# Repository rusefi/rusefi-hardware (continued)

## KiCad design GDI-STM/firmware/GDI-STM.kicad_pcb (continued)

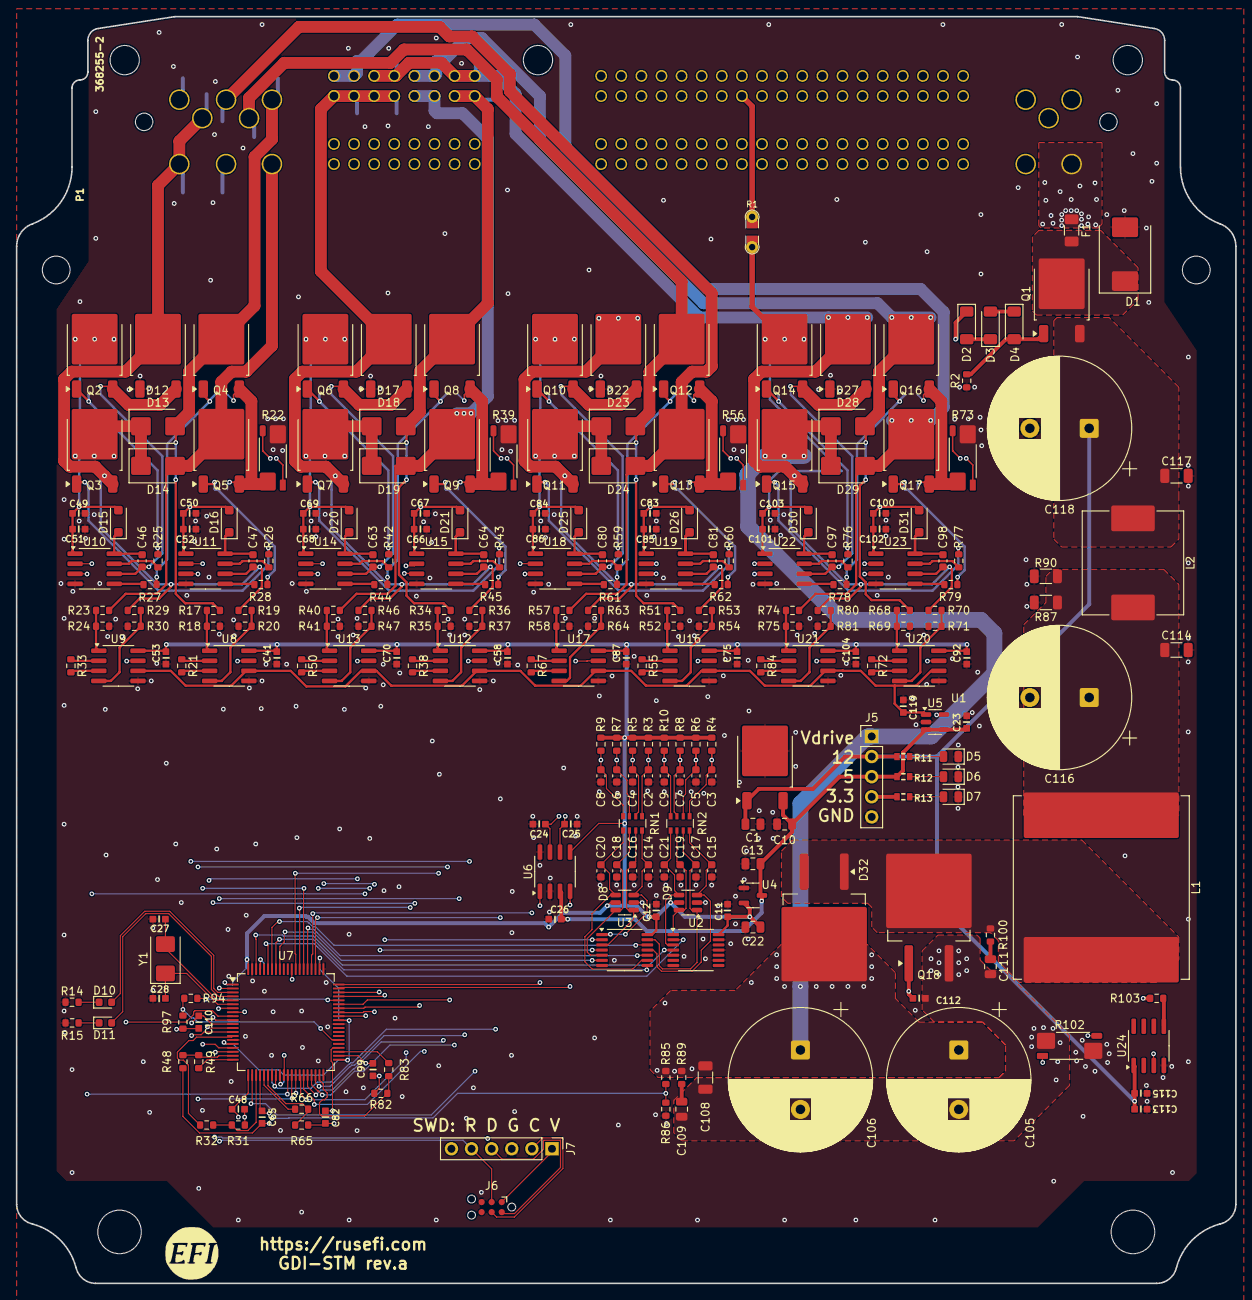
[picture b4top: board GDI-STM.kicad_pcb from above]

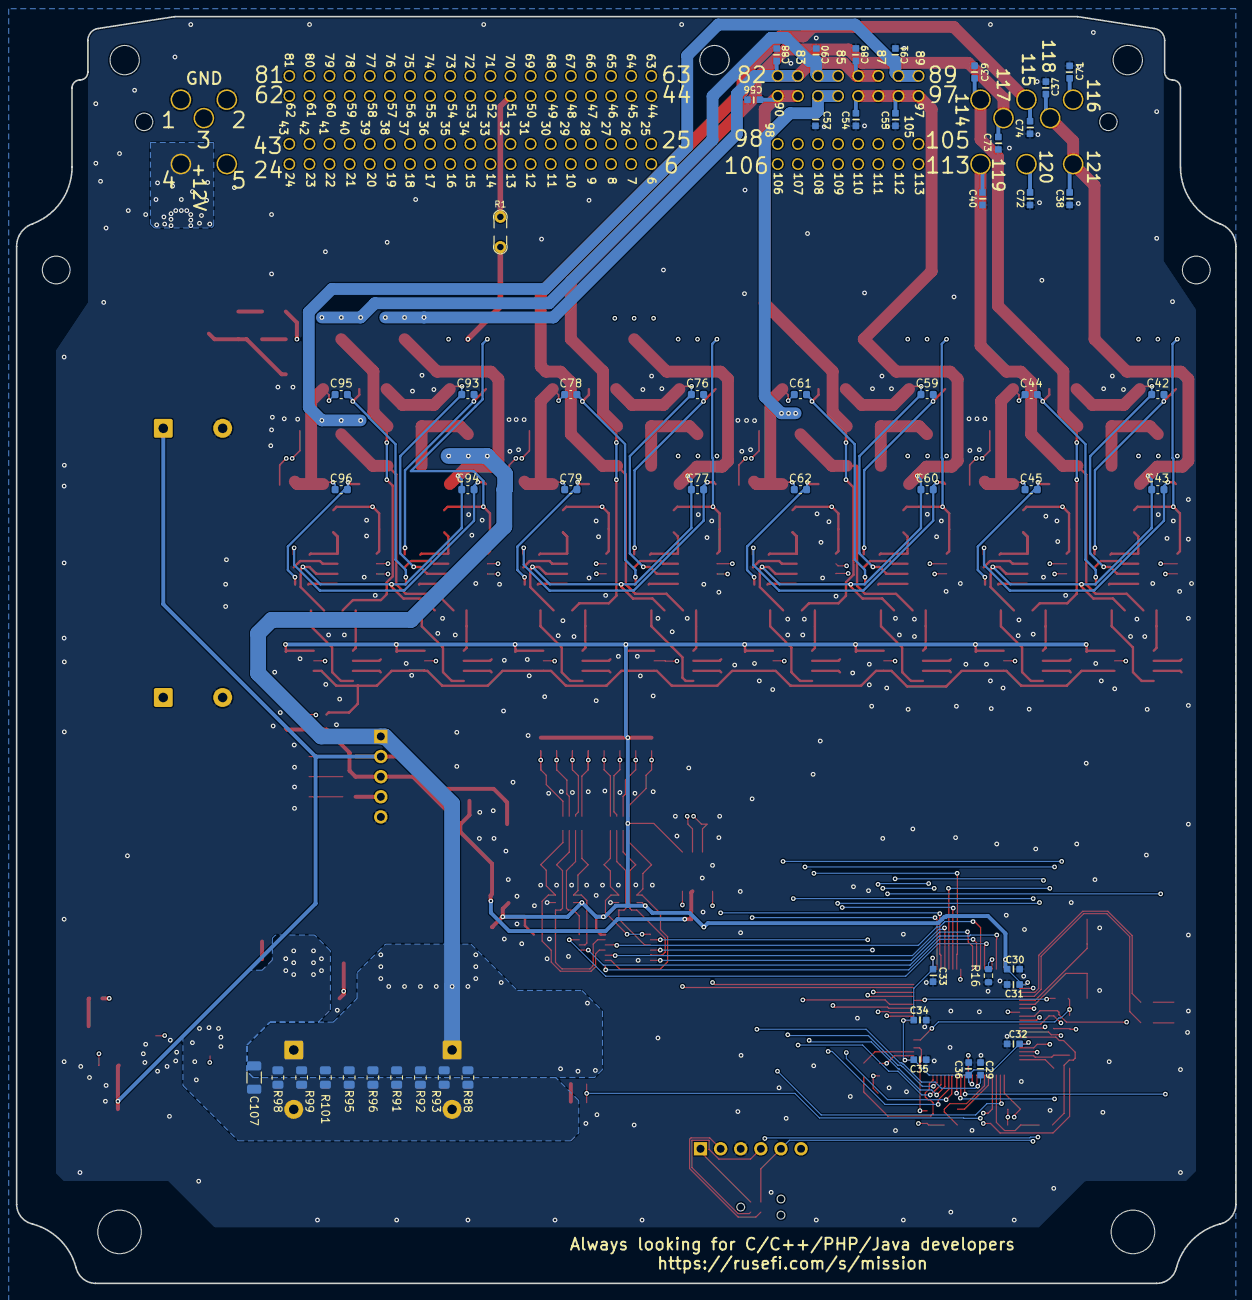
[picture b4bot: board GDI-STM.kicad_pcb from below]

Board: 4 copper layers, 154.0 x 160.0 mm, 311 parts (51 on the bottom side), 199 nets.

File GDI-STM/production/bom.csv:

Designator,Footprint,Quantity,Value,LCSC Part #
"C1, C10, C13, C22",0805,4,10u,C15850
"C100, C101, C113, C49, C50, C66, C67, C83, C84",C0603,9,1u,C15849
"C102, C103, C104, C11, C115, C119, C12, C23, C26, C29, C31, C32, C33, C34, C35, C36, C41, C51, C52, C53, C58, C68, C69, C70, C75, C85, C86, C87, C92",C0603,29,100n,C14663
"C105, C106",CP_Radial_D18.0mm_P7.50mm,2,470uF/200V,C160144
"C107, C108, C114, C117",1206,4,0.22uF,C106048
"C109, C111",0805,2,330p,C113837
"C110, C48, C65, C82, C99",C0603,5,330p,C576850
C112,C0603,1,470p,C326973
"C116, C118",CP_Radial_D18.0mm_P7.50mm,2,2200uF/50V,C106661
"C14, C15, C16, C17, C18, C19, C2, C20, C21, C3, C4, C42, C43, C44, C45, C5, C59, C6, C60, C61, C62, C7, C76, C77, C78, C79, C8, C9, C93, C94, C95, C96",0603,32,1000pF,C106247
"C24, C25",C0603,2,47p,C1671
"C27, C28",C0603,2,12p,C38523
C30,C0603,1,4.7u,C19666
"C37, C38, C39, C40, C54, C55, C56, C57, C71, C72, C73, C74, C88, C89, C90, C91",C0603,16,4700p,C327158
"C46, C47, C63, C64, C80, C81, C97, C98",0603,8,0.33uF,C1615
D1,D_SMC,1,SMCJ22CA,C151904
D10,0603,1,GREEN,C12624
D11,0603,1,RED,C2286
"D12, D17, D22, D27",TO-252-2,4,SBR10200CTL,C459529
"D13, D14, D18, D19, D23, D24, D28, D29",D_SMB,8,SS520B,C382826
"D15, D16, D20, D21, D25, D26, D30, D31",D_SOD-123F,8,ES1JFL,C719809
"D2, D3, D4",D_MiniMELF,3,ZMM5V6,C7497481
D32,TO-263-2,1,STTH802G-TR,C181034
"D5, D6, D7",0805,3,LED_Small,C2296
"D8, D9",SOT-23-6,2,SRV05-4,C85364
F1,1206,1,20A,C136357
L1,L_Changjiang_FXL2213,1,10uH,C22378757
L2,L_Changjiang_FXL1360,1,6.8uH,C7471128
P1,TE_368255-2,1,368255-2,
Q1,TO-252-2,1,AOD4185,C400894
"Q10, Q11, Q12, Q13, Q14, Q15, Q16, Q17, Q2, Q3, Q4, Q5, Q6, Q7, Q8, Q9",TO-252-2,16,IPD320N20N3G,C501515
Q18,TO-263-2,1,IPB107N20N3G,C444895
"R10, R14, R15, R18, R20, R24, R3, R30, R35, R37, R4, R41, R47, R5, R52, R54, R58, R6, R64, R69, R7, R71, R75, R8, R81, R86, R9",0603,27,1K,C21190
"R100, R89",0603,2,5.1,C25197
"R101, R88, R91, R92, R93, R95, R96, R98, R99",0805,9,360k,C17645
"R102, R22, R39, R56, R73",R_Shunt_Vishay_WSK2512_6332Metric_T1.19mm,5,0.016,C915978
"R103, R25, R26, R27, R28, R42, R43, R44, R45, R59, R60, R61, R62, R76, R77, R78, R79",0603,17,10,C22859
R11,R0603,1,5.1k,C23186
R12,R0603,1,1.6k,C22847
R13,R0603,1,750,C23241
"R16, R2",0603,2,10K,C25804
"R17, R19, R23, R29, R34, R36, R40, R46, R51, R53, R57, R63, R68, R70, R74, R80, R85",0603,17,147k,C22878
"R31, R48, R65, R82, R97",0603,5,1.02k,C22831
"R32, R49, R66, R83, R94",0603,5,7.15k,C25980
"R87, R90",1206,2,2K,C17944
"RN1, RN2",R_Array_Convex_4x0603,2,10k,C29718
U1,TO-252-2,1,LM78M05_TO252,C58069
"U10, U11, U14, U15, U18, U19, U22, U23, U24",SOIC-8_3.9x4.9mm_P1.27mm,9,IRS21867S,C52290
"U12, U13, U16, U17, U20, U21, U8, U9",SOIC-8_3.9x4.9mm_P1.27mm,8,INA826,C38433
"U2, U3",TSSOP-14_4.4x5mm_P0.65mm,2,74HC14,C5606
U4,SOT-23-3,1,XC6206P332MR,C5446
U5,SOT-23-5,1,REF2033,C440747
U6,SOIC-8_3.9x4.9mm_P1.27mm,1,TJA1051T-3,C38695
U7,LQFP-80_12x12mm_P0.5mm,1,STM32G474M_B-C-E_Tx,C5270364
Y1,Crystal_SMD_5032-2Pin_5.0x3.2mm,1,20MHz,C112566

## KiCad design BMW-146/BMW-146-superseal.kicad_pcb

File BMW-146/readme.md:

# N54

E9x 2006 to 2010 with "35" engine would be N54

For some years they had both N54 and N55 depending on trim. 335is would be N54, N55 would be newer engine with 204 pin ECU

https://rusefi.com/docs/pinouts/BMW-E92/

https://github.com/rusefi/rusefi_documentation/blob/master/OEM-Docs/Bmw/2010%20BMW%20335i%20Coupe%20(E92)%20N54.pdf

# offtopic

https://github.com/rusefi/rusefi_documentation/blob/master/OEM-Docs/Bmw/2009%20BMW%20328i%20Sedan%20(E90)%203.0%20N51.pdf

https://github.com/rusefi/rusefi_documentation/blob/master/OEM-Docs/Bmw/2009%20BMW%20335i%20Sedan%20(E90)%203.0%20N53.pdf

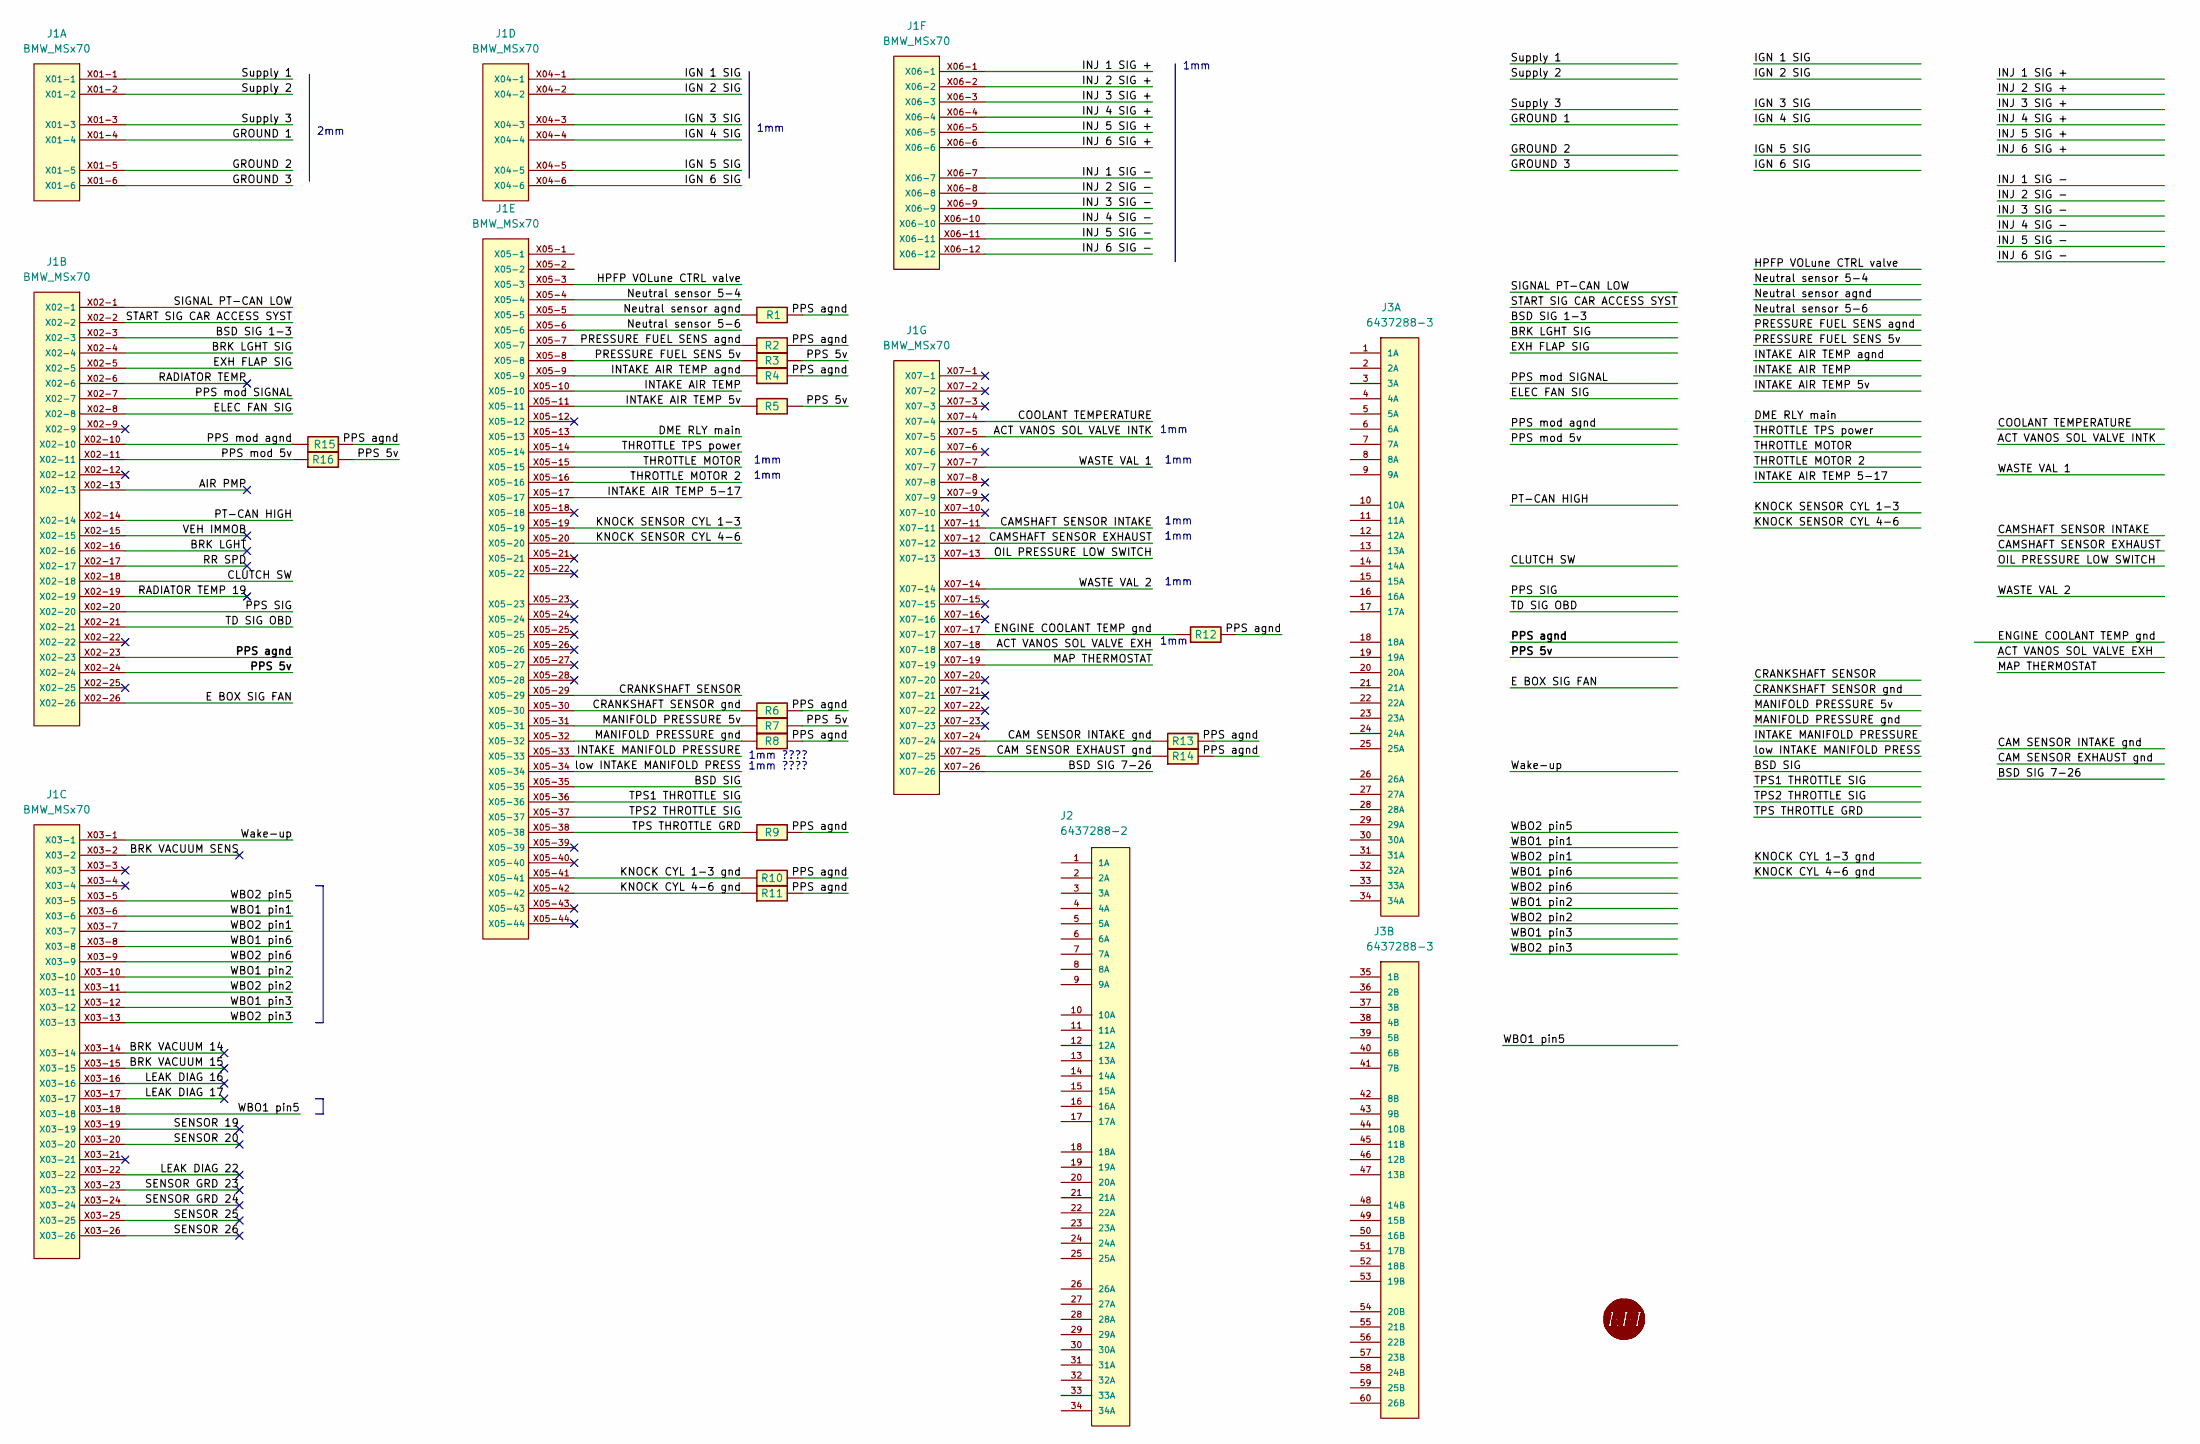
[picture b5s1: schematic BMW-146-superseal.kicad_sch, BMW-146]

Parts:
G1, G2: RUSEFI_LOGO; rusefi_logo
J1: BMW_MSx70
J2: 6437288-2; LCSC C591852
J3: 6437288-3; TE_6437288-3
R1, R2, R3, R4, R5, R6, R7, R8, R9, R10, R11, R12, R13, R14, R15, R16: 0R; R0603

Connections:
/ACT VANOS SOL VALVE EXH: J1.X07-18
/ACT VANOS SOL VALVE INTK: J1.X07-5
/AIR PMP: J1.X02-13
/BRK LGHT: J1.X02-16
/BRK LGHT SIG: J1.X02-4
/BRK VACUUM 14: J1.X03-14
/BRK VACUUM 15: J1.X03-15
/BRK VACUUM SENS: J1.X03-2
/BSD SIG: J1.X05-35
/BSD SIG 1-3: J1.X02-3
/BSD SIG 7-26: J1.X07-26
/CAM SENSOR EXHAUST gnd: J1.X07-25, R14.1
/CAM SENSOR INTAKE gnd: J1.X07-24, R13.1
/CAMSHAFT SENSOR EXHAUST: J1.X07-12
/CAMSHAFT SENSOR INTAKE: J1.X07-11
/CLUTCH SW: J1.X02-18
/COOLANT TEMPERATURE: J1.X07-4
/CRANKSHAFT SENSOR: J1.X05-29
/CRANKSHAFT SENSOR gnd: J1.X05-30, R6.1
/DME RLY main: J1.X05-13
/E BOX SIG FAN: J1.X02-26
/ELEC FAN SIG: J1.X02-8
/ENGINE COOLANT TEMP gnd: J1.X07-17, R12.1
/EXH FLAP SIG: J1.X02-5
/GROUND 1: J1.X01-4
/GROUND 2: J1.X01-5
/GROUND 3: J1.X01-6
/HPFP VOLune CTRL valve: J1.X05-3
/IGN 1 SIG: J1.X04-1
/IGN 2 SIG: J1.X04-2
/IGN 3 SIG: J1.X04-3
/IGN 4 SIG: J1.X04-4
/IGN 5 SIG: J1.X04-5
/IGN 6 SIG: J1.X04-6
/INJ 1 SIG +: J1.X06-1
/INJ 1 SIG -: J1.X06-7
/INJ 2 SIG +: J1.X06-2
/INJ 2 SIG -: J1.X06-8
/INJ 3 SIG +: J1.X06-3
/INJ 3 SIG -: J1.X06-9
/INJ 4 SIG +: J1.X06-4
/INJ 4 SIG -: J1.X06-10
/INJ 5 SIG +: J1.X06-5
/INJ 5 SIG -: J1.X06-11
/INJ 6 SIG +: J1.X06-6
/INJ 6 SIG -: J1.X06-12
/INTAKE AIR TEMP: J1.X05-10
/INTAKE AIR TEMP 5-17: J1.X05-17
/INTAKE AIR TEMP 5v: J1.X05-11, R5.1
/INTAKE AIR TEMP agnd: J1.X05-9, R4.1
/INTAKE MANIFOLD PRESSURE: J1.X05-33
/KNOCK CYL 1-3 gnd: J1.X05-41, R10.1
/KNOCK CYL 4-6 gnd: J1.X05-42, R11.1
/KNOCK SENSOR CYL 1-3: J1.X05-19
/KNOCK SENSOR CYL 4-6: J1.X05-20
/LEAK DIAG 16: J1.X03-16
/LEAK DIAG 17: J1.X03-17
/LEAK DIAG 22: J1.X03-22
/MANIFOLD PRESSURE 5v: J1.X05-31, R7.1
/MANIFOLD PRESSURE gnd: J1.X05-32, R8.1
/MAP THERMOSTAT: J1.X07-19
/Neutral sensor 5-4: J1.X05-4
/Neutral sensor 5-6: J1.X05-6
/Neutral sensor agnd: J1.X05-5, R1.1
/OIL PRESSURE LOW SWITCH: J1.X07-13
/PPS 5v: J1.X02-24, R3.2, R5.2, R7.2, R16.2
/PPS SIG: J1.X02-20
/PPS agnd: J1.X02-23, R1.2, R2.2, R4.2, R6.2, R8.2, R9.2, R10.2, R11.2, R12.2, R13.2, R14.2, R15.2
/PPS mod 5v: J1.X02-11, R16.1
/PPS mod SIGNAL: J1.X02-7
/PPS mod agnd: J1.X02-10, R15.1
/PRESSURE FUEL SENS 5v: J1.X05-8, R3.1
/PRESSURE FUEL SENS agnd: J1.X05-7, R2.1
/PT-CAN HIGH: J1.X02-14
/RADIATOR TEMP: J1.X02-6
/RADIATOR TEMP 19: J1.X02-19
/RR SPD: J1.X02-17
/SENSOR 19: J1.X03-19
/SENSOR 20: J1.X03-20
/SENSOR 25: J1.X03-25
/SENSOR 26: J1.X03-26
/SENSOR GRD 23: J1.X03-23
/SENSOR GRD 24: J1.X03-24
/SIGNAL PT-CAN LOW: J1.X02-1
/START SIG CAR ACCESS SYST: J1.X02-2
/Supply 1: J1.X01-1
/Supply 2: J1.X01-2
/Supply 3: J1.X01-3
/TD SIG OBD: J1.X02-21
/THROTTLE MOTOR: J1.X05-15
/THROTTLE MOTOR 2: J1.X05-16
/THROTTLE TPS power: J1.X05-14
/TPS1 THROTTLE SIG: J1.X05-36
/TPS2 THROTTLE SIG: J1.X05-37
/TPS THROTTLE GRD: J1.X05-38, R9.1
/VEH IMMOB: J1.X02-15
/WASTE VAL 1: J1.X07-7
/WASTE VAL 2: J1.X07-14
/WBO1 pin1: J1.X03-6
/WBO1 pin2: J1.X03-10
/WBO1 pin3: J1.X03-12
/WBO1 pin5: J1.X03-18
/WBO1 pin6: J1.X03-8
/WBO2 pin1: J1.X03-7
/WBO2 pin2: J1.X03-11
/WBO2 pin3: J1.X03-13
/WBO2 pin5: J1.X03-5
/WBO2 pin6: J1.X03-9
/Wake-up: J1.X03-1
/low INTAKE MANIFOLD PRESS: J1.X05-34

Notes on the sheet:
1mm
1mm ????
2mm

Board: 2 copper layers, 21 parts (1 on the bottom side), 18 nets, no tracks yet.

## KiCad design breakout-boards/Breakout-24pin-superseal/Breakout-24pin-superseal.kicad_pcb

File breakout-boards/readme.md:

# Vehicle to superseal adapter

Claim yours at https://shop.rusefi.com

* Ferrari-Maserati f136 engine 121 pins 

* Ford Mustang 198 pins

* [Hyundai 1.6 GDI PB 154 pins GDI](https://github.com/rusefi/rusefi-hardware/blob/main/breakout-boards/Breakout_154_kia_pb/hellen-hyundai-pb-154-adapter-b-schematic.pdf) [pinout](https://rusefi.com/docs/pinouts/hellen/hellen-hyundai-pb-mt/)

* Bosch me17 112 pins

* [Mazda Miata NC](https://github.com/rusefi/rusefi-hardware/blob/main/breakout-boards/Breakout-mazda-nc-0.1.pdf) [pinout](https://rusefi.com/docs/pinouts/miata-nc/)

* Mitsubishi Lancer Evo-x

* Mitsubishi Mirage

* Volkswagen Passat 2.0 MED9.1 154 pins GDI

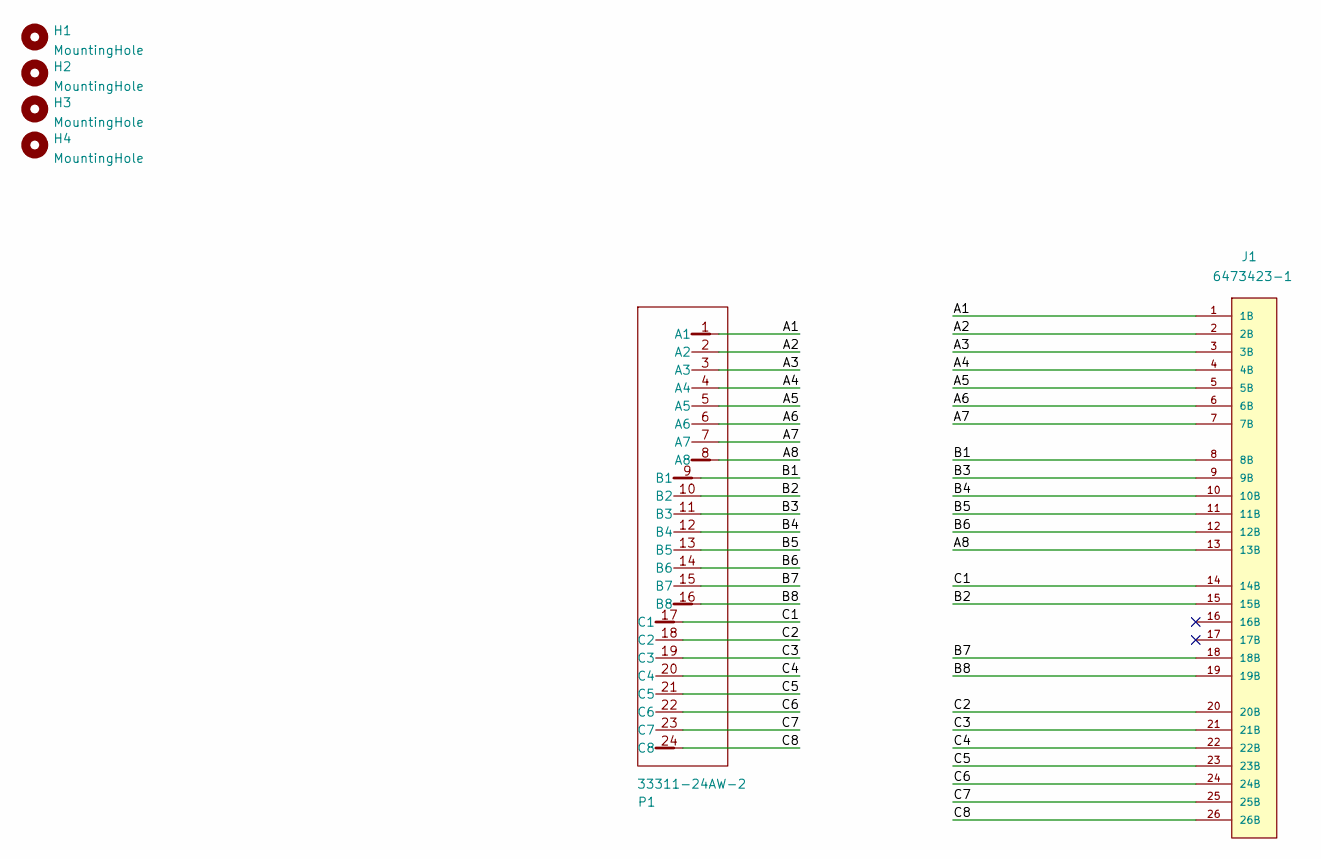
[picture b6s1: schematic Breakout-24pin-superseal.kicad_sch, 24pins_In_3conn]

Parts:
H1, H2, H3, H4: MountingHole; MountingHole_3.2mm_M3_DIN965_Pad
J1: 6473423-1
P1: 33311-24AW-2

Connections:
/A1: J1.1 (1B), P1.1 (A1)
/A2: J1.2 (2B), P1.2 (A2)
/A3: J1.3 (3B), P1.3 (A3)
/A4: J1.4 (4B), P1.4 (A4)
/A5: J1.5 (5B), P1.5 (A5)
/A6: J1.6 (6B), P1.6 (A6)
/A7: J1.7 (7B), P1.7 (A7)
/A8: J1.13 (13B), P1.8 (A8)
/B1: J1.8 (8B), P1.9 (B1)
/B2: J1.15 (15B), P1.10 (B2)
/B3: J1.9 (9B), P1.11 (B3)
/B4: J1.10 (10B), P1.12 (B4)
/B5: J1.11 (11B), P1.13 (B5)
/B6: J1.12 (12B), P1.14 (B6)
/B7: J1.18 (18B), P1.15 (B7)
/B8: J1.19 (19B), P1.16 (B8)
/C1: J1.14 (14B), P1.17 (C1)
/C2: J1.20 (20B), P1.18 (C2)
/C3: J1.21 (21B), P1.19 (C3)
/C4: J1.22 (22B), P1.20 (C4)
/C5: J1.23 (23B), P1.21 (C5)
/C6: J1.24 (24B), P1.22 (C6)
/C7: J1.25 (25B), P1.23 (C7)
/C8: J1.26 (26B), P1.24 (C8)

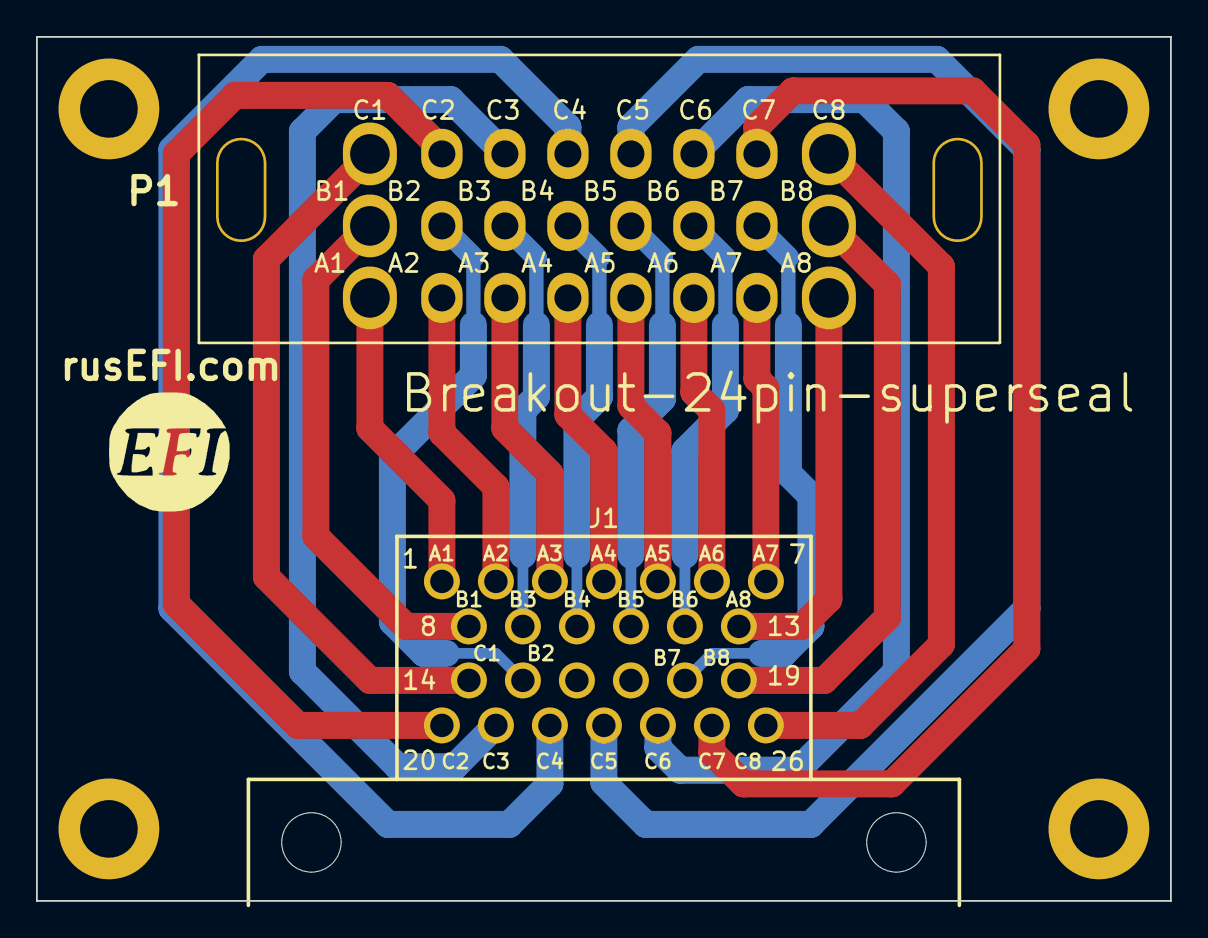
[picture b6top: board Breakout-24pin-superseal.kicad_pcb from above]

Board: 2 copper layers, 63.0 x 48.0 mm, 8 parts (1 on the bottom side), 24 nets.

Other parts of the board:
G?: LOGO
G?#2: LOGO

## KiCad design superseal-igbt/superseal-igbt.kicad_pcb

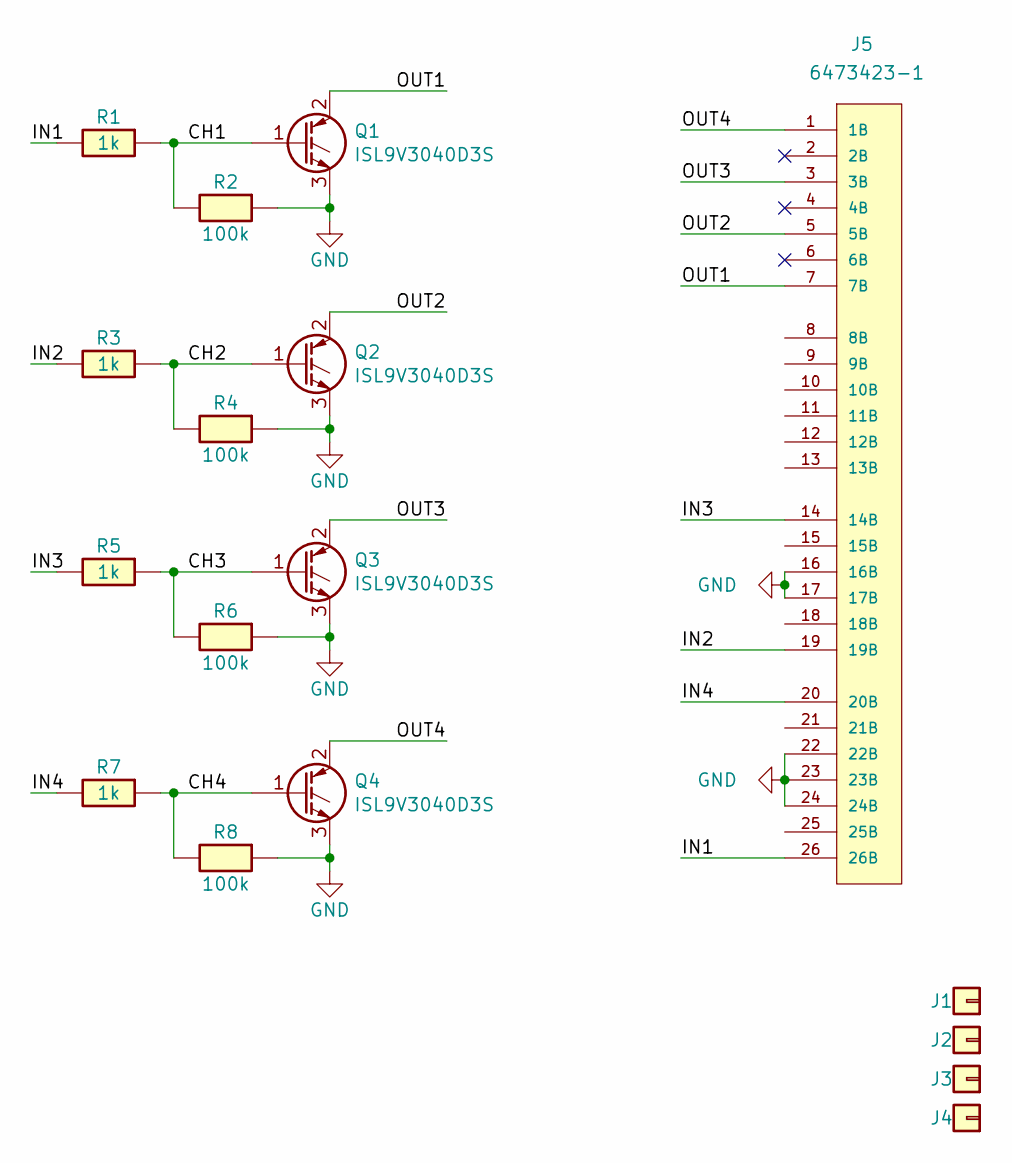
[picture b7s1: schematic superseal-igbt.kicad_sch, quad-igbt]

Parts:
J1, J2, J3, J4: Conn_01x01; MountingHole_5mm
J5: 6473423-1
Q1, Q2, Q3, Q4: ISL9V3040D3S; TO-263-2; LCSC C462128
R1, R3, R5, R7: 1k; R0805; LCSC C17513
R2, R4, R6, R8: 100k; R0805; LCSC C149504

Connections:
/CH1: Q1.1 (G), R1.1, R2.2
/CH2: Q2.1 (G), R3.1, R4.2
/CH3: Q3.1 (G), R5.1, R6.2
/CH4: Q4.1 (G), R7.1, R8.2
/IN1: J5.26 (26B), R1.2
/IN2: J5.19 (19B), R3.2
/IN3: J5.14 (14B), R5.2
/IN4: J5.20 (20B), R7.2
/OUT1: J5.7 (7B), Q1.2 (C)
/OUT2: J5.5 (5B), Q2.2 (C)
/OUT3: J5.3 (3B), Q3.2 (C)
/OUT4: J5.1 (1B), Q4.2 (C)
GND: J5.16 (16B), J5.17 (17B), J5.22 (22B), J5.23 (23B), J5.24 (24B), Q1.3 (E), Q2.3 (E), Q3.3 (E), Q4.3 (E), R2.1, R4.1, R6.1, R8.1

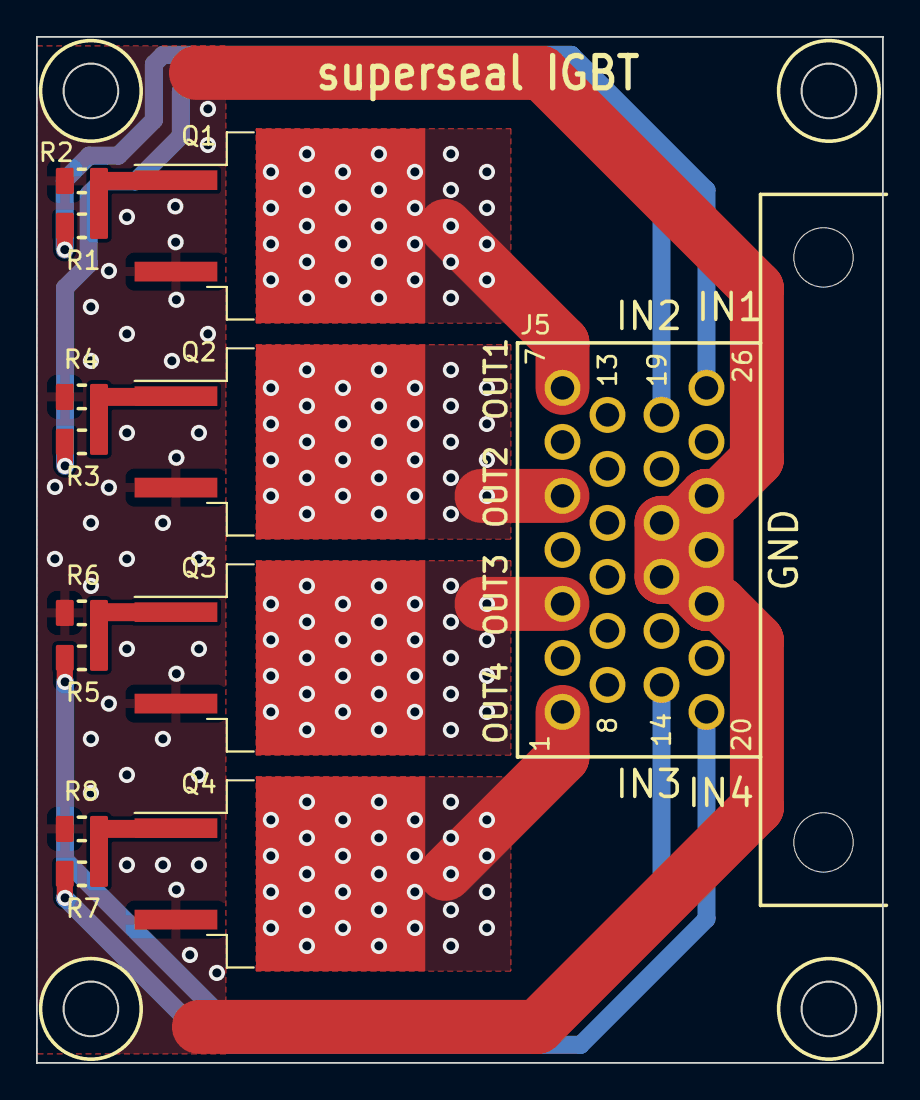
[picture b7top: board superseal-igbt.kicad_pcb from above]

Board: 2 copper layers, 47.0 x 57.0 mm, 17 parts (0 on the bottom side), 13 nets.

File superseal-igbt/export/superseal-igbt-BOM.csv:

Comment,Designator,Footprint,LCSC Part #
"6473423-1","J5","Connectors:6473423-1",""
"ISL9V3040D3S","Q1","Package_TO_SOT_SMD:TO-263-2","C462128"
"ISL9V3040D3S","Q2","Package_TO_SOT_SMD:TO-263-2","C462128"
"ISL9V3040D3S","Q3","Package_TO_SOT_SMD:TO-263-2","C462128"
"ISL9V3040D3S","Q4","Package_TO_SOT_SMD:TO-263-2","C462128"
"1k","R1","hellen-one-common:R0805","C17513"
"100k","R2","hellen-one-common:R0805","C149504"
"1k","R3","hellen-one-common:R0805","C17513"
"100k","R4","hellen-one-common:R0805","C149504"
"1k","R5","hellen-one-common:R0805","C17513"
"100k","R6","hellen-one-common:R0805","C149504"
"1k","R7","hellen-one-common:R0805","C17513"
"100k","R8","hellen-one-common:R0805","C149504"

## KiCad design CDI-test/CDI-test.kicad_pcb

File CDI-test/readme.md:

https://www.youtube.com/watch?v=ZHLb0ZEvTBY

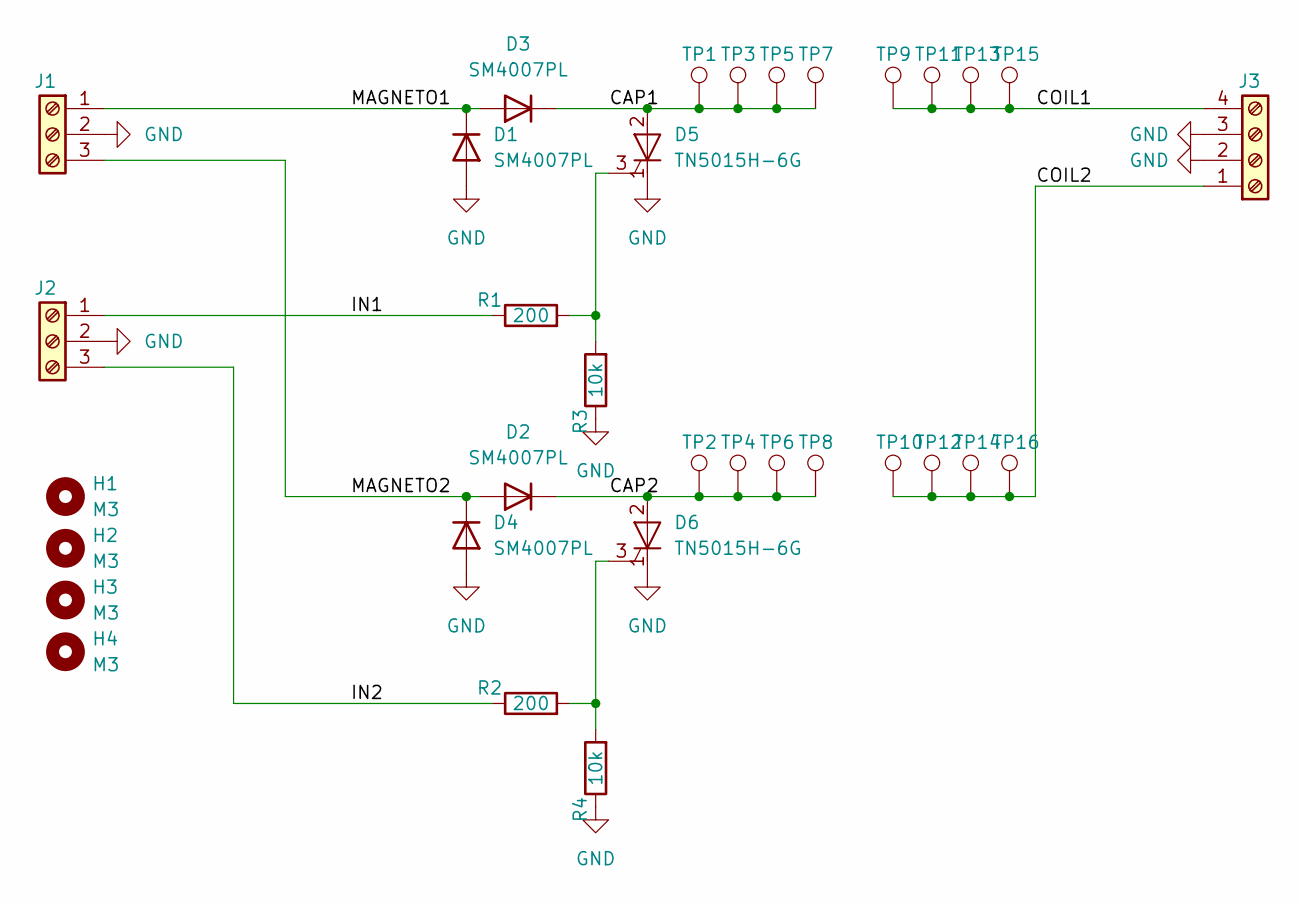
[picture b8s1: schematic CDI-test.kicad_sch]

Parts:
D1, D2, D3, D4: SM4007PL; D_SOD-123F; LCSC C64898
D5, D6: TN5015H-6G; TO-263-2; LCSC C2971185
H1, H2, H3, H4: M3; MountingHole_3.2mm_M3_Pad_Via
J1, J2: Screw_Terminal_01x03; TerminalBlock_MetzConnect_Type055_RT01503HDWU_1x03_P5.00mm_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; LCSC C557647
J3: Screw_Terminal_01x04; TerminalBlock_MetzConnect_Type055_RT01504HDWU_1x04_P5.00mm_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; LCSC C173286
R1, R2: 200; R_1206_3216Metric_Pad1.30x1.75mm_HandSolder; LCSC C2962216
R3, R4: 10k; R_1206_3216Metric_Pad1.30x1.75mm_HandSolder; LCSC C175515
TP1, TP2, TP3, TP4, TP5, TP6, TP7, TP8, TP9, TP10, TP11, TP12, TP13, TP14, TP15, TP16: SolderWire-1sqmm_1x01_D1.4mm_OD2.7mm

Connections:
/CAP1: D3.1 (K), D5.2 (A), TP1.1, TP3.1, TP5.1, TP7.1
/CAP2: D2.1 (K), D6.2 (A), TP2.1, TP4.1, TP6.1, TP8.1
/COIL1: J3.4, TP9.1, TP11.1, TP13.1, TP15.1
/COIL2: J3.1, TP10.1, TP12.1, TP14.1, TP16.1
/IN1: J2.1, R1.1
/IN2: J2.3, R2.1
/MAGNETO1: D1.1 (K), D3.2 (A), J1.1
/MAGNETO2: D2.2 (A), D4.1 (K), J1.3
GND: D1.2 (A), D4.2 (A), D5.1 (K), D6.1 (K), J1.2, J2.2, J3.2, J3.3, R3.1, R4.1
unnamed: D5.3 (G), R1.2, R3.2
unnamed: D6.3 (G), R2.2, R4.2

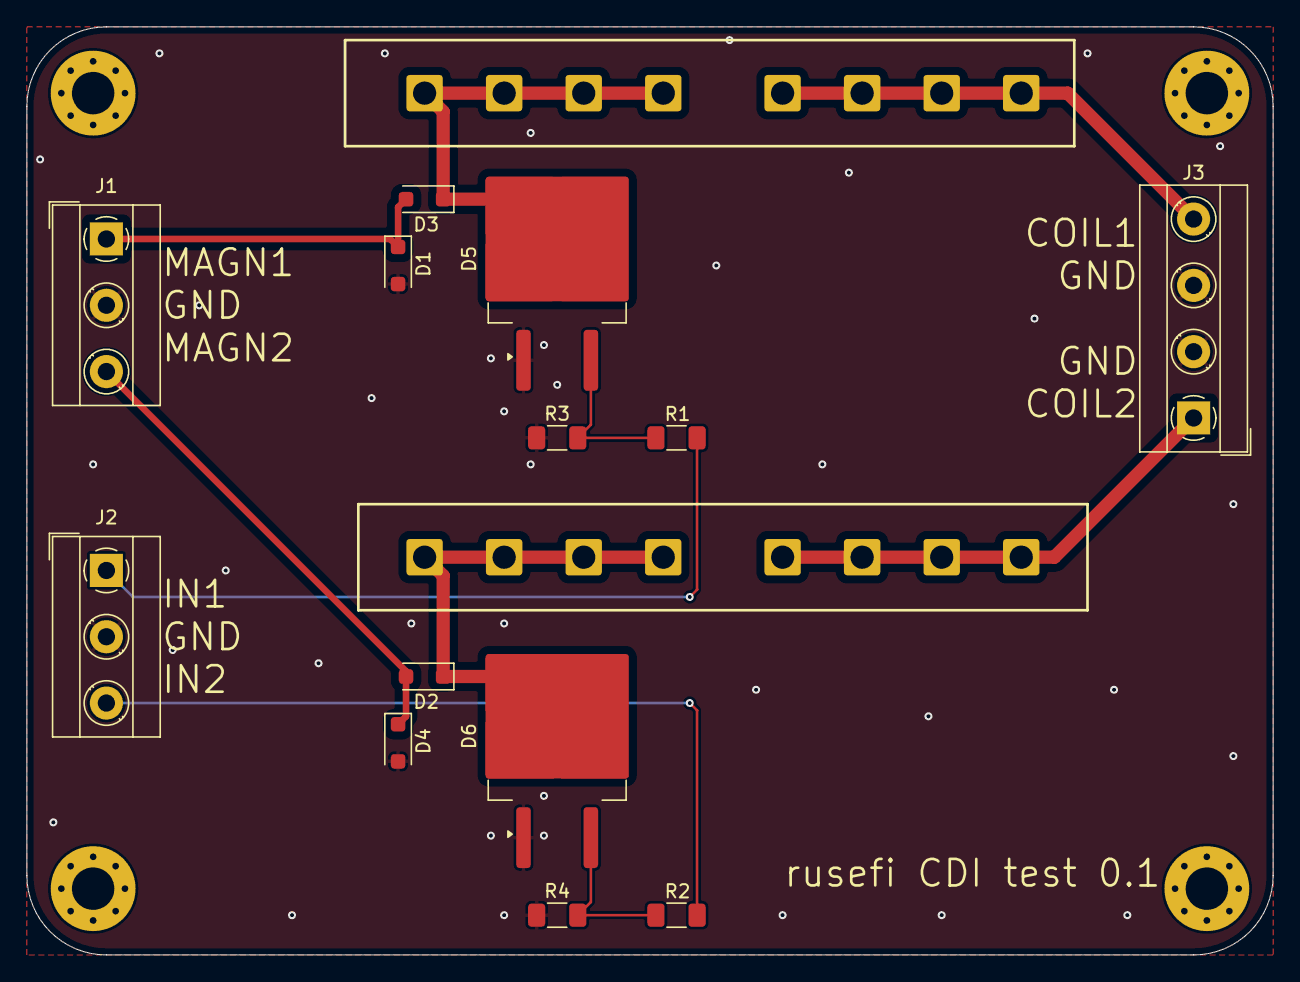
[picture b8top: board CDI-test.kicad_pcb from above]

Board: 2 copper layers, 94.0 x 70.0 mm, 33 parts (0 on the bottom side), 11 nets.

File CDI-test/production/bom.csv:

Designator,Footprint,Quantity,Value,LCSC Part #
"D1, D2, D3, D4",D_SOD-123F,4,SM4007PL,C64898
"D5, D6",TO-263-2,2,TN5015H-6G,C2971185
"J1, J2",TerminalBlock_MetzConnect_Type055_RT01503HDWU_1x03_P5.00mm_Horizontal,2,Screw_Terminal_01x03,C557647
J3,TerminalBlock_MetzConnect_Type055_RT01504HDWU_1x04_P5.00mm_Horizontal,1,Screw_Terminal_01x04,C173286
"R1, R2",1206,2,200,C2962216
"R3, R4",1206,2,10k,C175515
"TP1, TP10, TP11, TP12, TP13, TP14, TP15, TP16, TP2, TP3, TP4, TP5, TP6, TP7, TP8, TP9",SolderWire-1sqmm_1x01_D1.4mm_OD2.7mm,16,~,

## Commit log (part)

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2024-03-29 #261
2024-03-29 edit for JLS
2024-04-24 fresh
2024-05-02 US_TO_NT_MULTIPLIER=1
2024-05-02 bump
2024-05-03 progress
2024-05-04 WOW bugfix
2024-05-05 nissan is a good start
2024-05-10 something is broken
2024-05-13 BOARD_ID_154HYUNDAI_D
2024-05-13 gain_8_7
2024-06-02 we need to wake some boards up!
2024-06-07 aux pinout progress
2024-06-07 board_url
2024-06-12 colors
2024-06-25 totalErrorsCounter
2024-06-25 SILVER & BOARD_ID_154HYUNDAI_E
2024-06-26 STATIC_BOARD_ID_HELLEN_HD
2024-06-29 121vag
2024-07-07 121nissan
2024-07-08 121nissan huh?
2024-07-08 uaefi121
2024-07-10 totalGood
2024-07-18 warnings: "error"
2024-07-18 cid1
2024-07-18 kawa
2024-07-18 cid2
2024-07-18 cid3
2024-07-18 cid4
2024-07-18 cid5
2024-07-18 i am an idiot sorry
2024-07-28 a bit of a hack - lazy reuse for most basic pins
2024-07-29 POLARIS
2024-08-03 logging improvements
2024-08-04 jatco_g35
2024-08-11 4k-gdi
2024-08-11 4k-gdi sad
2024-08-13 moved to main repo
2024-08-25 BOARD_ID_HONDA125_E
2024-08-27 https://github.com/rusefi/rusefi/issues/6781 revive MC33816 driver, also support bus sharing #6781
2024-08-28 BOARD_ID_UAEFI_B weird
2024-08-29 Upd GDI6
2024-08-31 8chan stability
2024-08-31 uaefi121-sbc
2024-09-08 GDI6 export
2024-09-08 usability/progress?
2024-09-09 BOARD_ID_UAEFI121_B
2024-09-12 actually fresh lib with 8.7?
2024-09-12 compatible with older lib gain 8.7
2024-09-23 add coordinates
2024-09-23 pins
2024-09-23 pin34
2024-09-28 CDI test
2024-09-29 rename
2024-09-29 clean-up
2024-09-30 #273 X2 and #272 kiCad 7.0
2024-10-02 ops WBO were forgotten
2024-10-05 why not 0.8114
2024-10-09 GDI 6 rev b
2024-10-10 gdi6 fab
2024-10-18 https://github.com/rusefi/stim/issues/35
2024-10-18 version
2024-10-19 switching to rev C
2024-10-23 https://github.com/rusefi/rusefi/issues/6997
    extracting class
2024-10-23 https://github.com/rusefi/rusefi/issues/6997
    array of classes not array inside class
2024-10-23 https://github.com/rusefi/rusefi/issues/6997
    extracting read method
2024-10-26 I have a dream
2024-11-02 docs
2024-11-02 more detailed logging, extracting variables
2024-11-02 MAP range drama or not?
2024-11-06 photos
2024-11-22 typos
2024-11-22 sent_constants.h
2024-11-22 https://github.com/rusefi/rusefi/issues/6997
2024-12-12 much better location
2024-12-12 cid: main
2024-12-13 Integrate and enable SENT
2024-12-13 SENT: debug
2024-12-13 Serial is simplier that UART
2024-12-13 libfirmware: update, SENT decoder
2024-12-14 removing SENT
2024-12-14 removing SENT unit tests
2024-12-14 libfirmware: update SENT decoder
2024-12-14 SENT: decoder for GM pressure sensor
    Still TBD temperature encoding
2024-12-14 GDI4: transmit GM fuel pressure sensor data over can
2024-12-14 gdi4: update for libfirmware SENT
2024-12-14 aliveCounter
2024-12-14 SENT GM magic numbers
2024-12-17 GDI4: use different CAN IDs depending on ID pin
2024-12-17 GDI4: SENT to CAN: correct comment
2024-12-17 libfirmware: update
2025-01-05 first PT2000 commit, includes the dev studio project, and a loading code which was a slightly modified pt2001/mc33816 with some nuances. microcode changed to signal dc-dc with flag1 instead of flag0,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
2025-01-05 Build GDI6 Firmware
2025-01-05 fancy way to get GCC
2025-01-05 gdi6_gcc_version_check.c
2025-01-27 добавила недостающие пины в supra yaml #157
2025-01-29 GDI4: release RESETB signal and activate DRVEN in common code
    If more than one PT2001 is used
2025-01-29 GDI4: support multiple PT2001 chips
    PB3 is used as CS for second chip.
    BP4, PB5 control DRVEN and RESETB of both chips.
2025-02-04 JDY-33
2025-02-04 lambda-x2: update BOM
2025-02-06 lambda-x2: default BOM is for LSU4.9
2025-02-12 chuma
2025-02-12 so many new boards
2025-02-14 a bit wider range
2025-02-16 refactoring
2025-02-16 sometimes high sides go after low sides, sometimes there is an explicit start index for high side
2025-02-17 happy e92
2025-02-19 some more outputs
2025-02-21 outputNames
2025-02-23 gold
2025-03-04 E92: happy led
2025-03-07 GDI8 input CAN should be same for both #301
2025-03-07 WOW !! !! !! #302
2025-03-17 we have removed these extra statuses
2025-03-17 BOARD_ID_GDI4CHAN_B
2025-03-23 pt2001 periodicCallback
2025-03-26 canRxCounter
2025-03-31 wow bug?!
2025-04-09 Add initial ZF 8HP installation board design files (schematic, PCB, and Gerbers)
    - KiCad project for a drop-in replacement TCU board
    - Supports ZF 8HP variants: 8HP45/50/51/70/75/90/95
    - Includes schematic, layout, and production-ready Gerber files
    - Designed for solder-in installation inside the transmission case
2025-04-12 BOARD_ID_HONDA_OBD1_C
2025-04-12 8chan rev D 315/*?!?!*/
2025-04-12 happy obd1
2025-04-13 crank obd1
2025-05-02 explicit ZERO OUTPUTS CONFIGURED
2025-05-02 subaru
2025-05-03 SILVER
2025-05-03 GDI-4ch: blink error code, try to reinit chip on failure
2025-05-04 Update libfirmware Reference action
2025-05-04 GHA says update ext/libfirmware submodule
2025-05-07 making GDI magic more available
2025-05-07 GDI4_CAN_SET_DLC
2025-05-18 nano
2025-05-21 nano: CLT precision
2025-06-06 enum rename
2025-06-06 super-uaefi
2025-06-16 8chan-gm-gen4
2025-06-17 STATIC_BOARD_ID_HELLEN_E38
2025-06-19 glitch?
2025-06-19 undo GHA glitch poke
2025-06-19 name clarification
2025-06-21 helping build
2025-06-21 helping build: hello 2025
2025-06-27 analog inputs
2025-07-04 e38 wboUnitsCount
2025-07-10 super
2025-07-17 Init GDI-STM
2025-07-20 https://github.com/rusefi/fw-gdi-stm
2025-07-22 superseal igbt #206
2025-07-24 Upd SCH
2025-07-31 readme
2025-08-01 typo
2025-08-12 Upd GDI-STM
2025-08-18 wboStartIndex
2025-08-19 digital-inputs fw: hd allow more strint range for TPS1_2
2025-08-20 wideband-F103
2025-08-26 digital-inputs: fw: add PULLED_UP_RANGE macro
2025-08-26 digital-inputs: fw: MAX_ANALOG_CHANNELS extend to 32
2025-08-26 digital-inputs: fw: hd: add three more inputs
    With hacks
2025-08-27 digital-inputs: fw: HD add AT1 input test
2025-08-29 Upd PCB
2025-08-30 Same as Breakout-24pin but going into superseal
2025-08-30 Breakout-24pin to superseal #313
2025-11-01 missed name
2025-12-30 Update readme.md with additional image
2026-01-17 BMW-E92
2026-01-17 yaml
2026-01-17 1 and 2
2026-01-18 coordinates
2026-01-18 proteus N54 146
2026-01-20 BOARD_ID_NANO_A
2026-01-23 swapping 146
2026-01-23 5, 6
2026-01-26 154 progress
2026-01-26 145 progress
2026-01-28 BMW 146 в superseal #251
    заготовка
2026-01-29 BMW 146 в superseal отмена
    заготовка
2026-01-30 добавила координаты
2026-01-30 добавила выводы на картинку
2026-01-30 исправила
2026-02-02 EFI_BOARD_E92
2026-02-04 Update readme to highlight zero firmware status
    Added a note indicating that zero firmware exists for the hardware.
2026-02-09 Fix image tag in readme.md
    Updated image tag in the readme file.
2026-02-09 Update firmware release link in readme
    Updated the current stable firmware release information.
2026-02-19 gdi-stm firmware
2026-02-19 GDI-STM uses FreeRTOS
2026-02-19 some skeleton files
2026-02-19 gdi-stm firmware 2
2026-02-19 github action
2026-02-21 accuracy
2026-02-21 removing "three additional channels"
2026-02-28 clean up
2026-02-28 Fix remaining merge conflict markers in CMakeLists.txt
    Made-with: Cursor
2026-02-28 CI: init nested submodules for GDI-STM firmware build
2026-03-10 real life
2026-03-11 reducing BMW 146 confusion
2026-03-17 BMW N52 yaml #325
2026-03-18 Update right.yaml
    correct comments
2026-04-05 updated readme with more clarity
2026-04-21 Update readme with stm32flash installation instructions
    Added instructions for using stm32flash utility on Linux and Windows.
2026-04-21 Update instructions for flashing STM32 board
    Added step to apply power while holding BOOT0 button.
